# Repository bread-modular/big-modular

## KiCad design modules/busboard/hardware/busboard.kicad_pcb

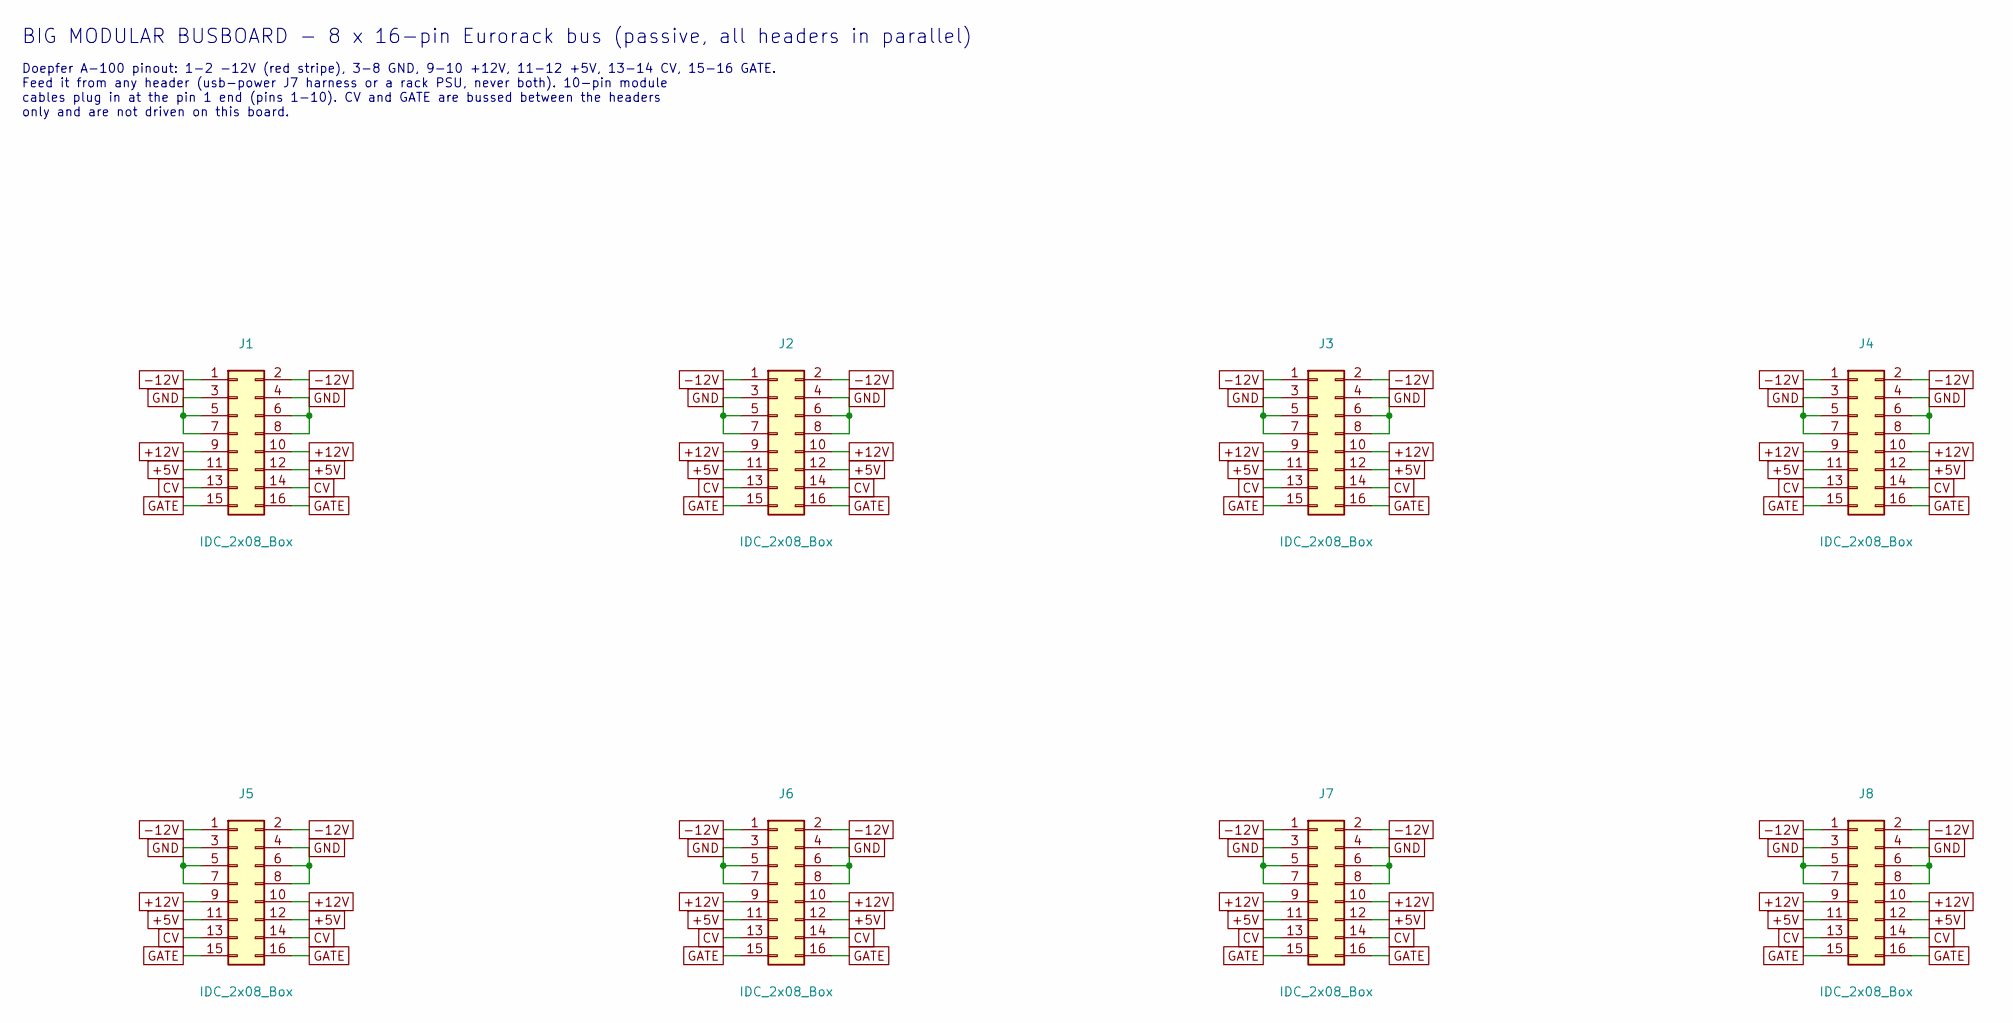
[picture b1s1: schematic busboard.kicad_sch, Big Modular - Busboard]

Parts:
J1, J2, J3, J4, J5, J6, J7, J8: IDC_2x08_Box; IDC-Header_2x08_P2.54mm_Vertical

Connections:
+5V: J1.11, J1.12, J2.11, J2.12, J3.11, J3.12, J4.11, J4.12, J5.11, J5.12, J6.11, J6.12, J7.11, J7.12, J8.11, J8.12
+12V: J1.9, J1.10, J2.9, J2.10, J3.9, J3.10, J4.9, J4.10, J5.9, J5.10, J6.9, J6.10, J7.9, J7.10, J8.9, J8.10
-12V: J1.1, J1.2, J2.1, J2.2, J3.1, J3.2, J4.1, J4.2, J5.1, J5.2, J6.1, J6.2, J7.1, J7.2, J8.1, J8.2
CV: J1.13, J1.14, J2.13, J2.14, J3.13, J3.14, J4.13, J4.14, J5.13, J5.14, J6.13, J6.14, J7.13, J7.14, J8.13, J8.14
GATE: J1.15, J1.16, J2.15, J2.16, J3.15, J3.16, J4.15, J4.16, J5.15, J5.16, J6.15, J6.16, J7.15, J7.16, J8.15, J8.16
GND: J1.3, J1.4, J1.5, J1.6, J1.7, J1.8, J2.3, J2.4, J2.5, J2.6, J2.7, J2.8, J3.3, J3.4, J3.5, J3.6, J3.7, J3.8, J4.3, J4.4, J4.5, J4.6, J4.7, J4.8, J5.3, J5.4, J5.5, J5.6, J5.7, J5.8, J6.3, J6.4, J6.5, J6.6, J6.7, J6.8, J7.3, J7.4, J7.5, J7.6, J7.7, J7.8, J8.3, J8.4, J8.5, J8.6, J8.7, J8.8

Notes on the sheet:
Doepfer A-100 pinout: 1-2 -12V (red stripe), 3-8 GND, 9-10 +12V, 11-12 +5V, 13-14 CV, 15-16 GATE. Feed it from any header (usb-power J7 harness or a rack PSU, never both). 10-pin module cables plug in at the pin 1 end (pins 1-10). CV and GATE are bussed between the headers only and are not driven o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
BIG MODULAR BUSBOARD - 8 x 16-pin Eurorack bus (passive, all headers in parallel)

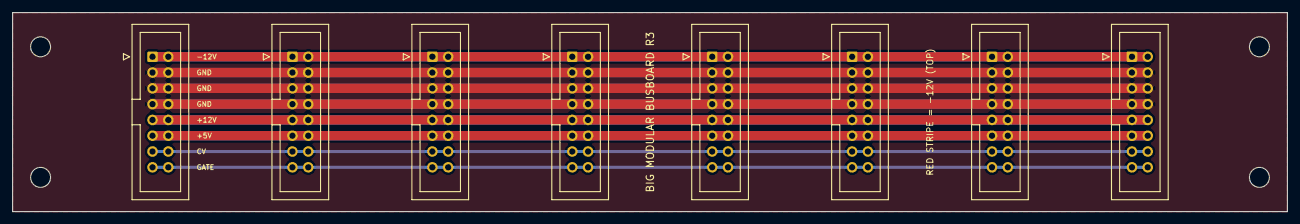
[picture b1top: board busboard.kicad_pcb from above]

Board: 2 copper layers, 205.0 x 32.0 mm, 8 parts (0 on the bottom side), 6 nets.

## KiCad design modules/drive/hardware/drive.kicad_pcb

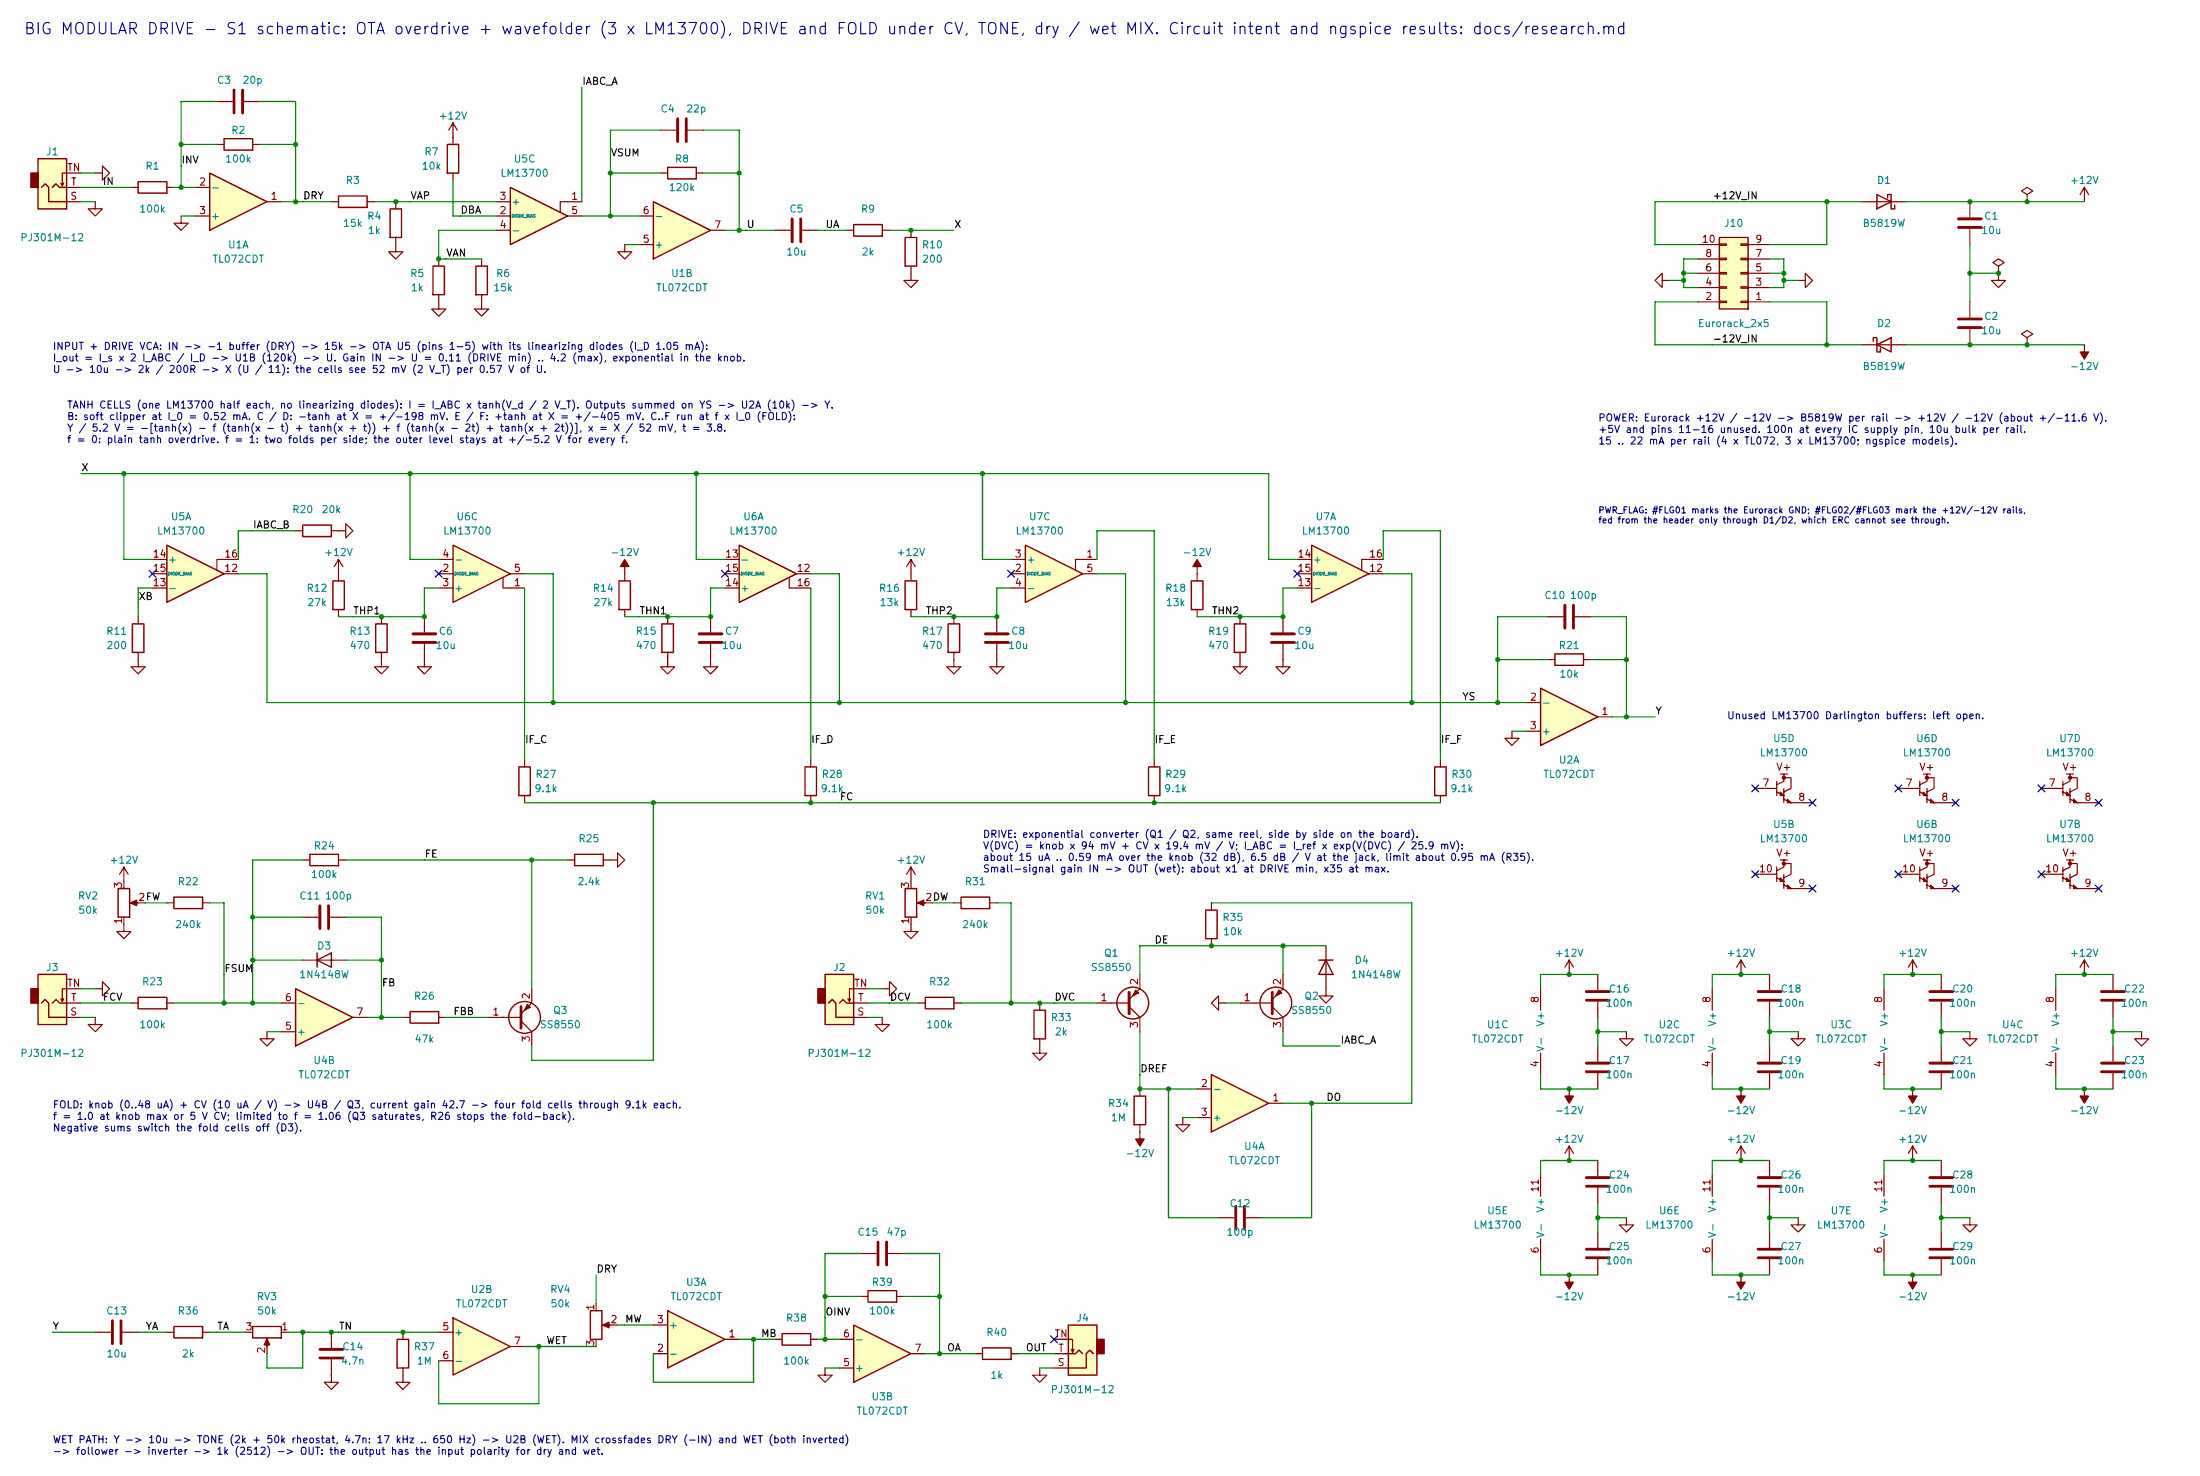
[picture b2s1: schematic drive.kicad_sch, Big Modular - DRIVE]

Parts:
C1, C2, C5, C6, C7, C8, C9, C13: 10u; C_0805_2012Metric; Voltage 25V; MPN CL21A106KAYNNNE; LCSC C15850
C3: 20p; C_0603_1608Metric; Voltage 50V; MPN CL10C200JB8NNNC; LCSC C1648
C4: 22p; C_0603_1608Metric; Voltage 50V; MPN CL10C220JB8NNNC; LCSC C1653
C10, C11, C12: 100p; C_0603_1608Metric; Voltage 50V; MPN CL10C101JB8NNNC; LCSC C14858
C14: 4.7n; C_0603_1608Metric; Voltage 50V; MPN 0603B472K500NT; LCSC C53987
C15: 47p; C_0603_1608Metric; Voltage 50V; MPN CL10C470JB8NNNC; LCSC C1671
C16, C17, C18, C19, C20, C21, C22, C23, C24, C25, C26, C27, C28, C29: 100n; C_0603_1608Metric; Voltage 50V; MPN CC0603KRX7R9BB104; LCSC C14663
D1, D2: B5819W; D_SOD-123; MPN B5819W SL; LCSC C8598
D3, D4: 1N4148W; D_SOD-123; MPN 1N4148W; LCSC C81598
J1, J2, J3, J4: PJ301M-12; Jack_3.5mm_QingPu_WQP-PJ301M-12_Vertical
J10: Eurorack_2x5; PinHeader_2x05_P2.54mm_Vertical
Q1, Q2, Q3: SS8550; SOT-23; MPN SS8550 Y2; LCSC C8542
R1, R2, R23, R24, R32, R38, R39: 100k; R_0603_1608Metric; MPN 0603WAF1003T5E; LCSC C25803
R3, R6: 15k; R_0603_1608Metric; MPN 0603WAF1502T5E; LCSC C22809
R4, R5: 1k; R_0603_1608Metric; MPN 0603WAF1001T5E; LCSC C21190
R7, R21, R35: 10k; R_0603_1608Metric; MPN 0603WAF1002T5E; LCSC C25804
R8: 120k; R_0603_1608Metric; MPN 0603WAF1203T5E; LCSC C25808
R9, R33, R36: 2k; R_0603_1608Metric; MPN 0603WAF2001T5E; LCSC C22975
R10, R11: 200; R_0603_1608Metric; MPN 0603WAF2000T5E; LCSC C8218
R12, R14: 27k; R_0603_1608Metric; MPN 0603WAF2702T5E; LCSC C22967
R13, R15, R17, R19: 470; R_0603_1608Metric; MPN 0603WAF4700T5E; LCSC C23179
R16, R18: 13k; R_0603_1608Metric; MPN 0603WAF1302T5E; LCSC C22797
R20: 20k; R_0603_1608Metric; MPN 0603WAF2002T5E; LCSC C4184
R22, R31: 240k; R_0603_1608Metric; MPN 0603WAF2403T5E; LCSC C4197
R25: 2.4k; R_0603_1608Metric; MPN 0603WAF2401T5E; LCSC C22940
R26: 47k; R_0603_1608Metric; MPN 0603WAF4702T5E; LCSC C25819
R27, R28, R29, R30: 9.1k; R_0603_1608Metric; MPN 0603WAF9101T5E; LCSC C23260
R34, R37: 1M; R_0603_1608Metric; MPN 0603WAF1004T5E; LCSC C22935
R40: 1k; R_2512_6332Metric; MPN 25121WF1001T4E; LCSC C54315
RV1, RV2, RV3, RV4: 50k; Potentiometer_RV09
U1, U2, U3, U4: TL072CDT; SOIC-8_3.9x4.9mm_P1.27mm; MPN TL072CDT; LCSC C6961
U5, U6, U7: LM13700; SOIC-16_3.9x9.9mm_P1.27mm; MPN LM13700MX/NOPB; LCSC C174050

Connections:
+12V: C1.1, C16.1, C18.1, C20.1, C22.1, C24.1, C26.1, C28.1, D1.1 (K), R7.1, R12.1, R16.1, RV1.3, RV2.3, U1.8 (V+), U2.8 (V+), U3.8 (V+), U4.8 (V+), U5.11 (V+), U6.11 (V+), U7.11 (V+)
-12V: C2.2, C17.2, C19.2, C21.2, C23.2, C25.2, C27.2, C29.2, D2.2 (A), R14.1, R18.1, R34.2, U1.4 (V-), U2.4 (V-), U3.4 (V-), U4.4 (V-), U5.6 (V-), U6.6 (V-), U7.6 (V-)
/+12V_IN: D1.2 (A), J10.9, J10.10
/-12V_IN: D2.1 (K), J10.1, J10.2
/DBA: R7.2, U5.2 (DIODE_BIAS)
/DCV: J2.T, R32.1
/DE: D4.1 (K), Q1.2 (E), Q2.2 (E), R35.2
/DO: C12.2, R35.1, U4.1
/DREF: C12.1, Q1.3 (C), R34.1, U4.2 (-)
/DRY: C3.2, R2.2, R3.1, RV4.1, U1.1
/DVC: Q1.1 (B), R31.2, R32.2, R33.1
/DW: R31.1, RV1.2
/FB: C11.2, D3.2 (A), R26.1, U4.7
/FBB: Q3.1 (B), R26.2
/FC: Q3.3 (C), R27.2, R28.2, R29.2, R30.2
/FCV: J3.T, R23.1
/FE: Q3.2 (E), R24.2, R25.1
/FSUM: C11.1, D3.1 (K), R22.2, R23.2, R24.1, U4.6 (-)
/FW: R22.1, RV2.2
/IABC_A: Q2.3 (C), U5.1
/IABC_B: R20.1, U5.16
/IF_C: R27.1, U6.1
/IF_D: R28.1, U6.16
/IF_E: R29.1, U7.1
/IF_F: R30.1, U7.16
/IN: J1.T, R1.1
/INV: C3.1, R1.2, R2.1, U1.2 (-)
/MB: R38.1, U3.1, U3.2 (-)
/MW: RV4.2, U3.3 (+)
/OA: C15.2, R39.2, R40.1, U3.7
/OINV: C15.1, R38.2, R39.1, U3.6 (-)
/OUT: J4.T, R40.2
/TA: R36.2, RV3.3
/THN1: C7.1, R14.2, R15.1, U6.14 (+)
/THN2: C9.1, R18.2, R19.1, U7.13 (-)
/THP1: C6.1, R12.2, R13.1, U6.3 (+)
/THP2: C8.1, R16.2, R17.1, U7.4 (-)
/TN: C14.1, R37.1, RV3.1, RV3.2, U2.5 (+)
/U: C4.2, C5.1, R8.2, U1.7
/UA: C5.2, R9.1
/VAN: R5.1, R6.1, U5.4 (-)
/VAP: R3.2, R4.1, U5.3 (+)
/VSUM: C4.1, R8.1, U1.6 (-), U5.5
/WET: RV4.3, U2.6 (-), U2.7
/X: R9.2, R10.1, U5.14 (+), U6.4 (-), U6.13 (-), U7.3 (+), U7.14 (+)
/XB: R11.1, U5.13 (-)
/Y: C10.2, C13.1, R21.2, U2.1
/YA: C13.2, R36.1
/YS: C10.1, R21.1, U2.2 (-), U5.12, U6.5, U6.12, U7.5, U7.12
GND: C1.2, C2.1, C6.2, C7.2, C8.2, C9.2, C14.2, C16.2, C17.1, C18.2, C19.1, C20.2, C21.1, C22.2, C23.1, C24.2, C25.1, C26.2, C27.1, C28.2, C29.1, D4.2 (A), J1.S, J1.TN, J2.S, J2.TN, J3.S, J3.TN, J4.S, J10.3, J10.4, J10.5, J10.6, J10.7, J10.8, Q2.1 (B), R4.2, R5.2, R6.2, R10.2, R11.2, R13.2, R15.2, R17.2, R19.2, R20.2, R25.2, R33.2, R37.2, RV1.1, RV2.1, U1.3 (+), U1.5 (+), U2.3 (+), U3.5 (+), U4.3 (+), U4.5 (+)

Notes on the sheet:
DRIVE: exponential converter (Q1 / Q2, same reel, side by side on the board). V(DVC) = knob x 94 mV + CV x 19.4 mV / V; I_ABC = I_ref x exp(V(DVC) / 25.9 mV): about 15 uA .. 0.59 mA over the knob (32 dB), 6.5 dB / V at the jack, limit about 0.95 mA (R35). Small-signal gain IN -> OUT (wet): about x1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
INPUT + DRIVE VCA: IN -> -1 buffer (DRY) -> 15k -> OTA U5 (pins 1-5) with its linearizing diodes (I_D 1.05 mA): I_out = I_s x 2 I_ABC / I_D -> U1B (120k) -> U. Gain IN -> U = 0.11 (DRIVE min) .. 4.2 (max), exponential in the knob. U -> 10u -> 2k / 200R -> X (U / 11): the cells see 52 mV (2 V_T) per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
FOLD: knob (0..48 uA) + CV (10 uA / V) -> U4B / Q3, current gain 42.7 -> four fold cells through 9.1k each. f = 1.0 at knob max or 5 V CV; limited to f = 1.06 (Q3 saturates, R26 stops the fold-back). Negative sums switch the fold cells off (D3).
Unused LM13700 Darlington buffers: left open.
POWER: Eurorack +12V / -12V -> B5819W per rail -> +12V / -12V (about +/-11.6 V). +5V and pins 11-16 unused. 100n at every IC supply pin, 10u bulk per rail. 15 .. 22 mA per rail (4 x TL072, 3 x LM13700; ngspice models).
TANH CELLS (one LM13700 half each, no linearizing diodes): I = I_ABC x tanh(V_d / 2 V_T). Outputs summed on YS -> U2A (10k) -> Y. B: soft clipper at I_0 = 0.52 mA. C / D: -tanh at X = +/-198 mV. E / F: +tanh at X = +/-405 mV. C..F run at f x I_0 (FOLD): Y / 5.2 V = -[tanh(x) - f (tanh(x - t) + tanh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
PWR_FLAG: #FLG01 marks the Eurorack GND; #FLG02/#FLG03 mark the +12V/-12V rails, fed from the header only through D1/D2, which ERC cannot see through.
BIG MODULAR DRIVE - S1 schematic: OTA overdrive + wavefolder (3 x LM13700), DRIVE and FOLD under CV, TONE, dry / wet MIX. Circuit intent and ngspice results: docs/research.md
WET PATH: Y -> 10u -> TONE (2k + 50k rheostat, 4.7n: 17 kHz .. 650 Hz) -> U2B (WET). MIX crossfades DRY (-IN) and WET (both inverted) -> follower -> inverter -> 1k (2512) -> OUT: the output has the input polarity for dry and wet.

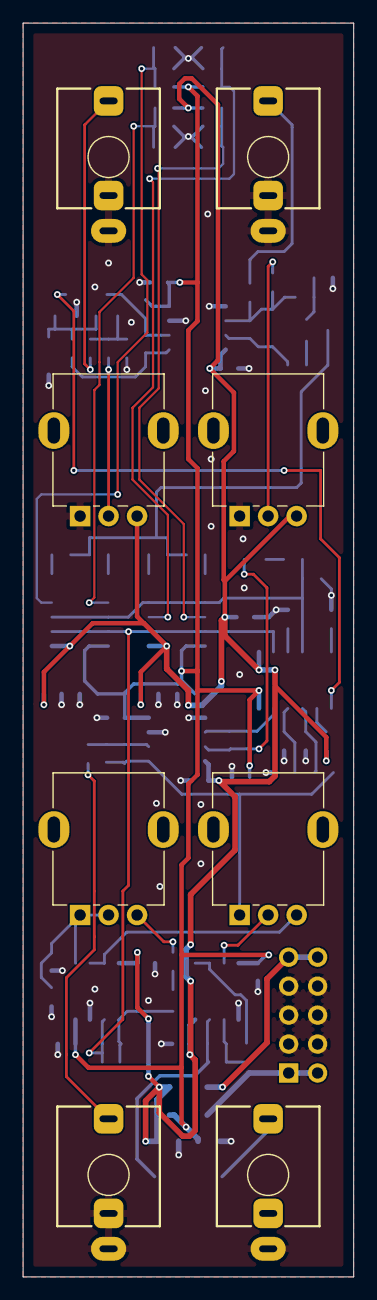
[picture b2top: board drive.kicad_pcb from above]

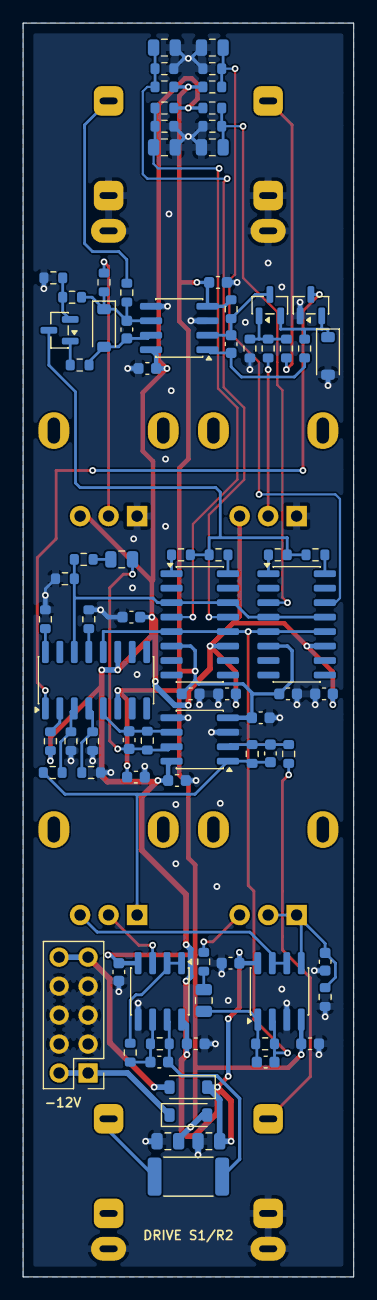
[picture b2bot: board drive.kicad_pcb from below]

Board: 2 copper layers, 29.0 x 110.0 mm, 92 parts (84 on the bottom side), 50 nets.
